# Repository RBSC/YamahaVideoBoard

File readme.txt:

Improved Video Board for Yamaha MSXs version 1.2
Copyright (c) 2016-2023 RBSC

About
-----

This is the improved video board for Yamaha YIS503II, YIS503III and similar MSX/MSX2 computers to replace the original video
boards or the older versions of the video boards from RBSC. The changes to the v1.2 board comparing to the previous verions are:

- Allows to use either CXA1675 or CXA2075 video encoder chips
- Contains an improved YTRAP filter
- Allows to use through-hole electrolytic capacitors (see note below)
- Allows to switch between on-board and internal MSX's 3.58MHz clock generator for NTSC
- Allows to disable one or both on-board clock generators
- Requires less components if CXA2075 encoder is used
- If using only computer's 3.58Mhz and NTSC, there's no need to assemble both clock generators

It is possible to use some components from the old black-and-white video board from the YIS503IIIR computer to build the v1.2
board. The following components can be re-used:

- 330uF capacitors (4)
- 10uF capacitors (4)
- 2sc1684 transistors (4)
- 100uF capacitors (2)
- DIN8 female socket
- Male 13-pin connector for motherboard's cable

IMPORTANT! When installing 100uF capacitors from the original board, please make sure to install the 16v rated capacitor as C3
and the 10v rated capacitor as C2. Otherwise, the 10v rated capacitor installed as C3 may blow up!

WARNING!
--------

Do not install ONBOARD and EXT jumpers at the same time! When using the EXT jumper, disable both NTSC and PAL clock generators
with their respective jumpers (see below).

The pinout of the RGB connector on the new video board differs from the original pinout! On the new board pin 3 is connected to
+12v supply. When making RGB to SCART cables or when using such cables designed for the Japanese MSX mashines, please make sure
that you connect the +12v to the correct SCART pin - pin 8. Connecting +12v to this pin will switch the TV/monitor to 4:3 mode.

DO NOT connect the cable from Yamaha YIS805 to this video board! The pin order is different on the YIS805 and you will damage
the board if you connect it to YIS805!

It is advised to power down the computer before switching between PAL and NTSC in order to avoid damage to the encoder chip.

Settings
--------

Compared to v1.1 of the videoboard, there are more jumpers. The jumpers labeled as PAL or NTSC DISABLE are used to disable the
on-board PAL or NTSC clock generators and use the internal computer's 3.58MHz clock for NTSC encoding. The installed jumper
disables the clock generator.

The ONBOARD and EXT jumpers are used to select which clock to use for NTSC encoding. When using the EXT jumper, the computer's
internal 3.58MHz clock will be fed to the encoder chip. This will effectively eliminate all color atrefacts in the composite
video output. But this will work only with NTSC mode. The installed jumper enables either on-board or external clock signal.
Never install both jumpers at the same time! Please note that the jumper settings do not affect the RGB output.

There are three 3-pin mode selection jumpers on the video board. These jumpers are used to set the color encoding for the S-Video
and composite video outputs. All 3 jumpers must be set the same way. When the pins 1-2 of the jumpers are shorted, the NTSC
encoding is enabled. Otherwise, when pins 2-3 of the jumpers are shorted, the PAL encoding is enabled. Please note that the
jumper settings do not affect the RGB output.

When setting up the board, it's recommended to measure the voltages on the outputs of 4 potentiometers (variable resistors). The
measurement should be done on the central pin. The correct voltage setting is required to form the stable picture on the
composite video and S-Video outputs.

When using the CXA1675 encoder chip, the recommended voltage for the CSYNC variable resistor is 1.3v, the recommended voltages
for Red, Green and Blue variable resistors are from 1.5v to 2.0v, depending on the desired brightness. The voltages on R, G and
B channels must be the same to avoid color distortion. Each color should be tuned after setting it as background color - for
example when setting the blue color's voltage, use the "color15,4,4" command in Basic to set blue as background color. For
green color use the "color15,2,2" command and for red color use the "color15,6,6" command.

When using the CXA2075 encoder chip, the voltage for CSYNC variable resistor should be set to 1.5v and the voltages for Red,
Green and Blue variable resistors should be set up to 3.0v to reach the desired brightness.

Notes
-----

When using the CXA2075 video encoder, it's not neccessary to install the following elements: C22, C23, C26, C27, R25, R29, R30.
Also, if L1 is not installed, please bridge its solder pads with a wire. However, it's highly recommended to use L1 for better
results.

When planning to use only NTSC encoding with the internal MSX's clock, it may not be necessary to install both oscillators,
both trim capacitors, 74HCT04 chip, C31, C13, C19, R17, R20, R23, as well as optional capacitors on the back side of the board.

Please use the following oscillators: 3.579MHz for NTSC and 4.433MHz for PAL. Using other oscillators may cause undesired side
effects.

It is recommended to use the 74HCT04 chip for the frequency generator circuit. The HC series chips may also work, but the HCT
series is highly recommended.

There may be artefacts on the color transitions in the composite video's output when using the on-board clock generators. These
artefacts can be removed by carefully adjusting the corresponding trim capacitors (C14 or C20) with a small flat screwdriver. 

The sharpness of the composite video output can be adjusted by the C23 trim capacitor that is marked as "YTRAP". Please use a
small flat screwdriver with an isolated handle to trim the capacitors, otherwise interference will occur.

If you are using a jumper pin header instead of the original cable connector, be careful to connect the cable from the MSX's
main board correctly. Incorrect cable connection may damage the video board and your MSX computer!

IMPORTANT!
----------

The RBSC provides all the files and information for free, without any liability (see the disclaimer.txt file). The provided information,
software or hardware must not be used for commercial purposes unless permitted by the RBSC. Producing a small amount of bare boards for
personal projects and selling the rest of the batch is allowed without the permission of RBSC.

When the sources of the tools are used to create alternative projects, please always mention the original source and the copyright!

Contact information
-------------------

The members of RBSC group Tnt23, Wierzbowsky, Pyhesty, Ptero, GreyWolf, SuperMax, VWarlock and DJS3000 can be contacted via the group's
e-mail address:

info@rbsc.su

The group's coordinator could be reached via this e-mail address:

admin@rbsc.su

The group's website can be found here:

https://rbsc.su/
https://rbsc.su/ru

The RBSC's hardware repository can be found here:

https://github.com/rbsc

The RBSC's 3D model repository can be found here:

https://www.thingiverse.com/groups/rbsc/things

-= ! MSX FOREVER ! =-

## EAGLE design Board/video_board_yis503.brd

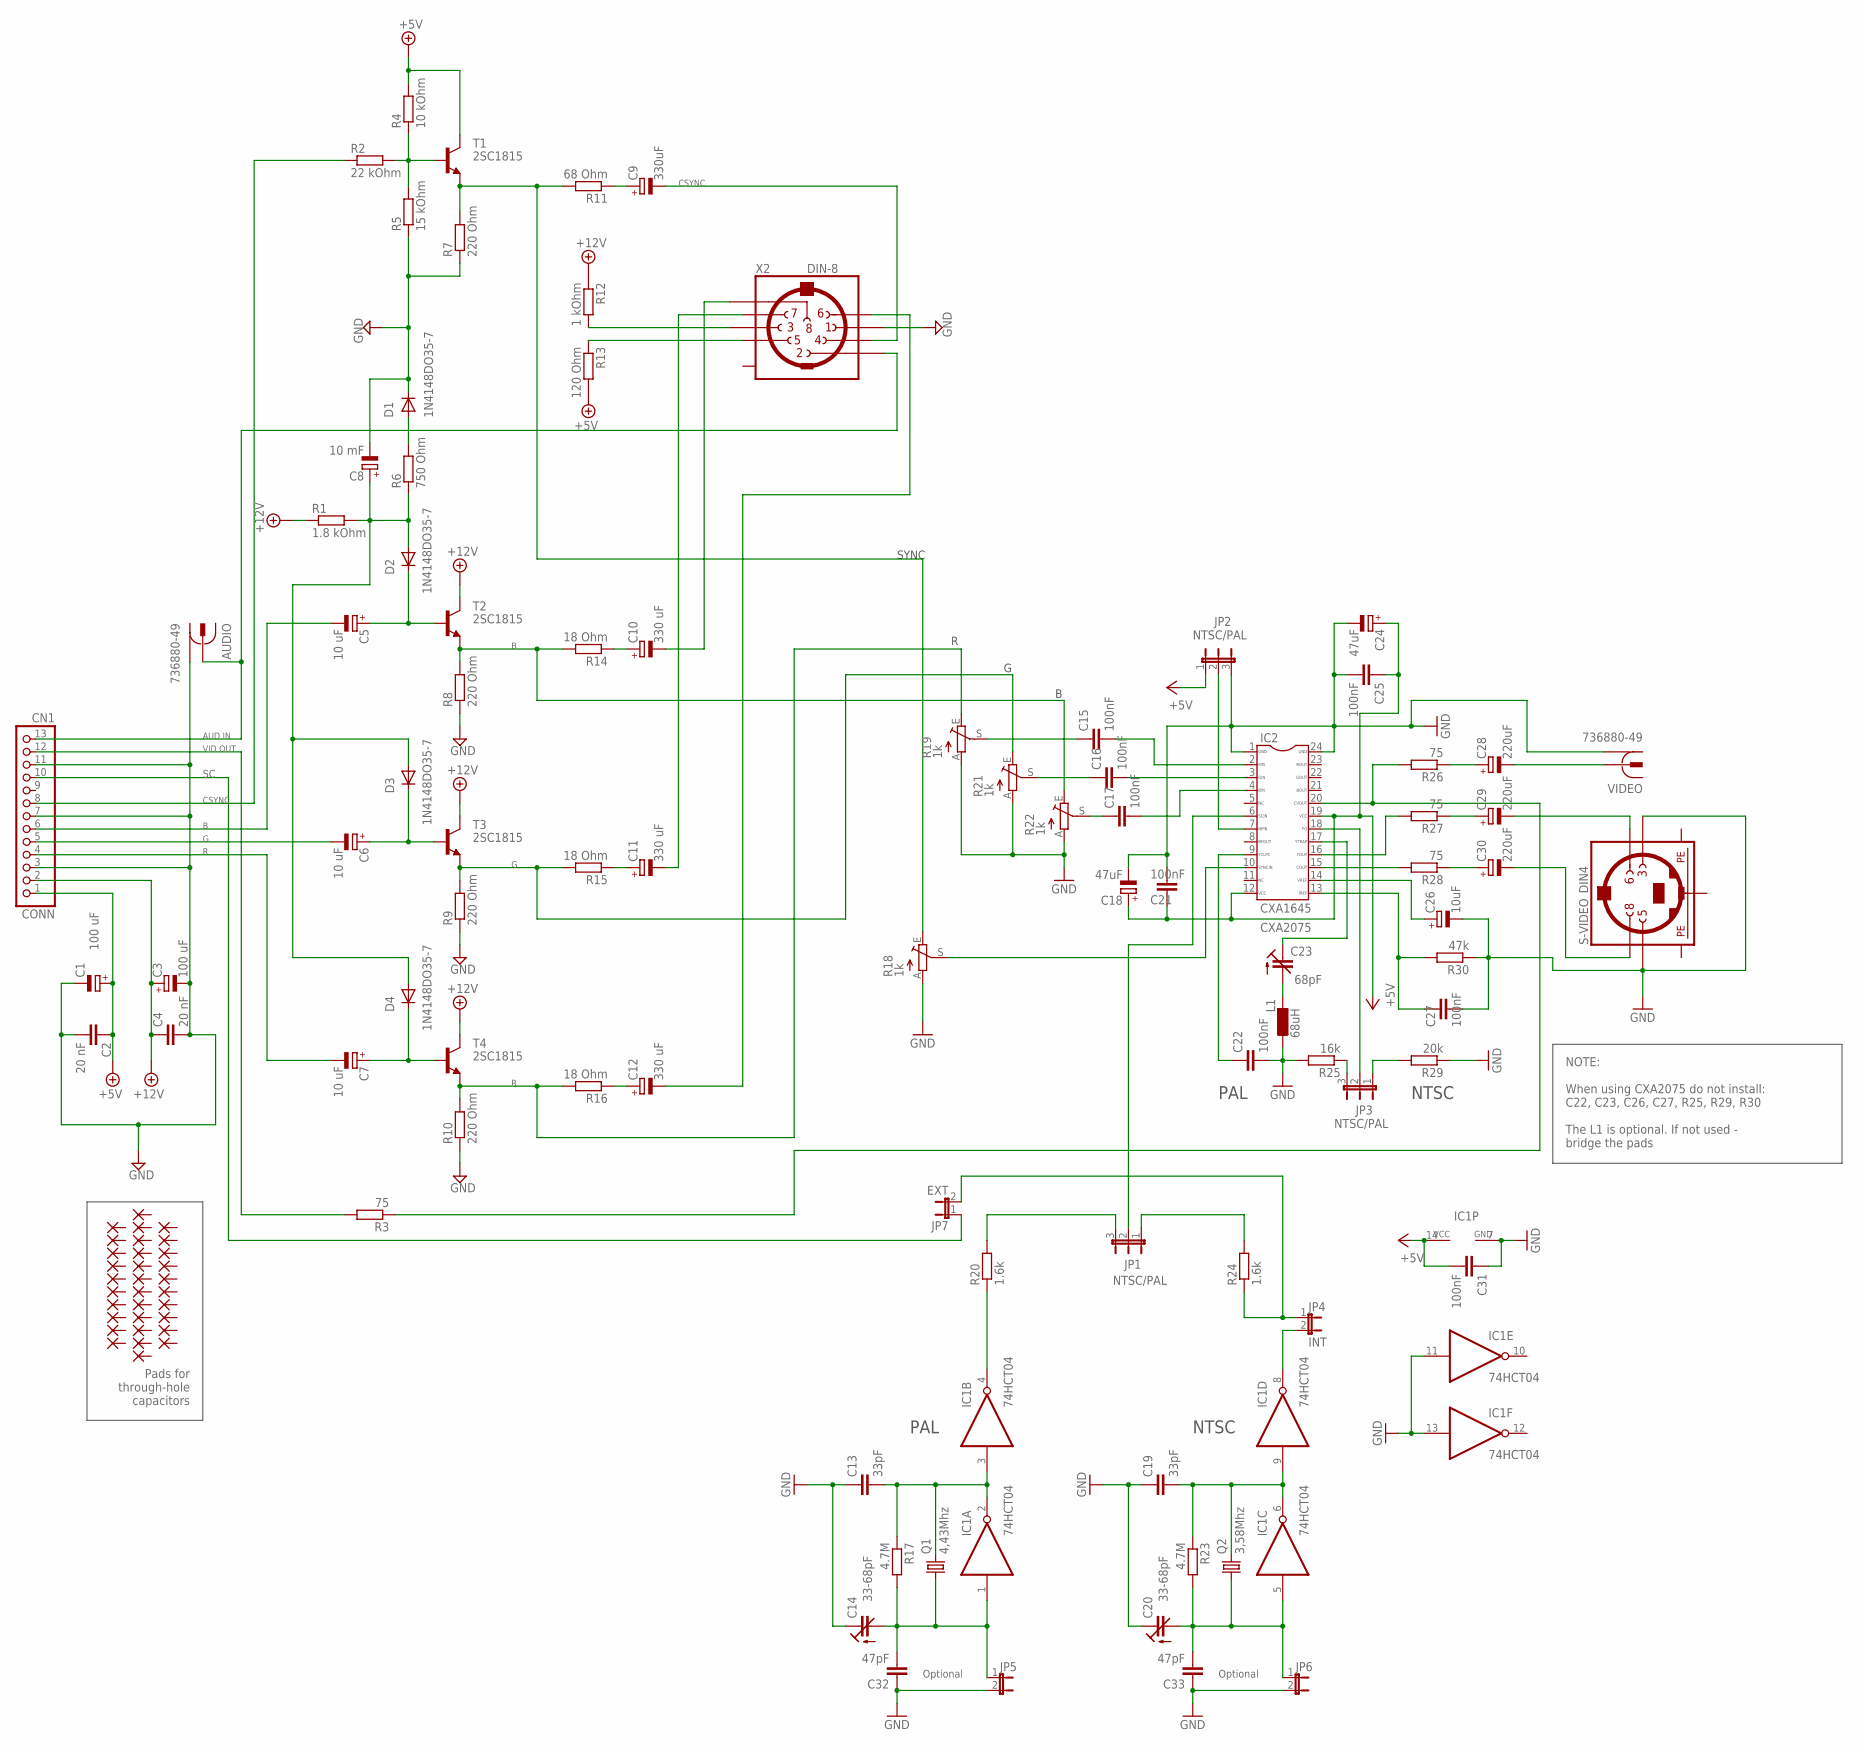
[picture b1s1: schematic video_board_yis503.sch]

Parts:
AUDIO: 736880-49
C1, C3: 100 uF; SMC_D
C2, C4: 20 nF; C0805
C5, C6, C7: 10 uF; SMC_B
C8: 10 mF; SMC_B
C9: 330uF; SMC_D
C10, C11, C12: 330 uF; SMC_D
C13, C19: 33pF; C0805
C14, C20: 33-68pF; CTRIMTZ03
C15, C16, C17, C21, C22, C25, C27, C31: 100nF; C0805
C18, C24: 47uF; SMC_B
C23: 68pF; CTRIMTZ03
C26: 10uF; SMC_B
C28, C29, C30: 220uF; SMC_D
C32, C33: 47pF; C0805
CONN: CN1; 1X13
D1, D2, D3, D4: 1N4148DO35-7; MINIMELF
IC1: 74HCT04; SO14
IC2: CXA1645; SOP24
JP1, JP2, JP3: NTSC/PAL; JP2
JP4: INT; JP1
JP5, JP6: JP1E; JP1
JP7: EXT; JP1
L1: 68uH; L3230M
P1, P2, P3, P4, P5, P6, P7, P8, P9, P10, P11, P12, P13, P14, P15, P16, P17, P18, P19, P20, P21, P22, P23, P24, P25, P26, P27, P28, P29, P30, P31, P32: PADTH
Q1: 4,43Mhz; HC49/S; MPN HC49SM-3.6864-30-50-60-16-ATF
Q2: 3,58Mhz; HC49/S; MPN HC49SM-3.6864-30-50-60-16-ATF
R1: 1.8 kOhm; R0805
R2: 22 kOhm; R0805
R3, R26, R27, R28: 75; R0805
R4: 10 kOhm; R0805
R5: 15 kOhm; R0805
R6: 750 Ohm; R0805
R7, R8, R9, R10: 220 Ohm; R0805
R11: 68 Ohm; R0805
R12: 1 kOhm; R0805
R13: 120 Ohm; R0805
R14, R15, R16: 18 Ohm; R0805
R17, R23: 4.7M; R0805
R18, R19, R21, R22: 1k; CA6V
R20, R24: 1.6k; R0805
R25: 16k; R0805
R29: 20k; R0805
R30: 47k; R0805
S-VIDEO: DIN4; M_DIN4
T1, T2, T3, T4: 2SC1815; TO92-ECB
VIDEO: 736880-49
X2: DIN-8; DIN8

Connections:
+5V: C1.+, C2.1, C18.+, C21.1, C24.+, C25.1, C31.2, CONN.1, IC1.14 (VCC), IC2.12, IC2.19, JP2.1, R4.2, R13.2, T1.C
+12V: C3.+, C4.1, CONN.2, R1.1, R12.1, T2.C, T3.C, T4.C
GND: AUDIO.1, AUDIO.1@1 (1), AUDIO.1@2 (1), C1.-, C2.2, C3.-, C4.2, C8.-, C13.1, C14.1 (E), C18.-, C19.1, C20.1 (E), C21.2, C22.2, C24.-, C25.2, C26.-, C27.2, C31.1, C32.1, C33.1, CONN.3, CONN.7, CONN.11, D1.C, IC1.7 (GND), IC1.11 (I), IC1.13 (I), IC2.1, IC2.24, JP2.3, JP5.2, JP6.2, L1.2, R5.1, R7.1, R8.1, R9.1, R10.1, R18.A, R19.A, R21.A, R22.A, R25.2, R29.1, R30.1, S-VIDEO.3, S-VIDEO.5, VIDEO.1, VIDEO.1@1 (1), VIDEO.1@2 (1), X2.1
unnamed: R10.2, R16.2, R19.E, T4.E
unnamed: C20.2 (A), C33.2, IC1.5 (I), JP6.1, Q2.1, R23.2
unnamed: JP4.1, JP7.2, R24.1
unnamed: CONN.8, R2.1
unnamed: R8.2, R14.2, R22.E, T2.E
unnamed: C15.1, R19.S
unnamed: C16.1, R21.S
unnamed: IC1.4 (O), R20.1
unnamed: C23.2 (A), L1.1
unnamed: C19.2, IC1.6 (O), IC1.9 (I), Q2.2, R23.1
unnamed: JP1.3, R20.2
unnamed: C8.+, D2.A, D3.A, D4.A, R1.2, R6.1
unnamed: JP3.3, R25.1
unnamed: IC2.7, JP2.2
unnamed: JP3.1, R29.2
unnamed: IC2.16, R27.2
unnamed: JP1.1, R24.2
unnamed: IC1.8 (O), JP4.2
unnamed: CONN.12, R3.2
unnamed: C23.1 (E), IC2.17
unnamed: C12.-, X2.6
unnamed: C11.-, X2.7
unnamed: C6.+, D3.C, T3.B
unnamed: C10.-, X2.8
unnamed: D1.A, R6.2
unnamed: C6.-, CONN.5
unnamed: C5.-, CONN.6
unnamed: AUDIO.2, CONN.13, X2.2
unnamed: C12.+, R16.1
unnamed: R12.2, X2.3
unnamed: R9.2, R15.2, R21.E, T3.E
unnamed: R13.1, X2.5
unnamed: C7.+, D4.C, T4.B
unnamed: C7.-, CONN.4
unnamed: C5.+, D2.C, T2.B
unnamed: R2.2, R4.1, R5.2, T1.B
unnamed: R7.2, R11.2, R18.E, T1.E
unnamed: C11.+, R15.1
unnamed: C10.+, R14.1
unnamed: C9.+, R11.1
unnamed: C9.-, X2.4
unnamed: C17.1, R22.S
unnamed: C16.2, IC2.3
unnamed: C15.2, IC2.2
unnamed: C17.2, IC2.4
unnamed: C14.2 (A), C32.2, IC1.1 (I), JP5.1, Q1.1, R17.2
unnamed: C13.2, IC1.2 (O), IC1.3 (I), Q1.2, R17.1
unnamed: IC2.10, R18.S
unnamed: IC2.6, JP1.2
unnamed: IC2.20, R3.1, R26.2
unnamed: C22.1, IC2.9
unnamed: IC2.18, JP3.2
unnamed: IC2.15, R28.2
unnamed: C28.+, R26.1
unnamed: C29.+, R27.1
unnamed: C30.+, R28.1
unnamed: C26.+, IC2.14
unnamed: C27.1, IC2.13, R30.2
unnamed: C28.-, VIDEO.2
unnamed: C29.-, S-VIDEO.6
unnamed: C30.-, S-VIDEO.8
PE1: S-VIDEO.SH1 (PE1)
PE2: S-VIDEO.SH2 (PE2)
PE3: S-VIDEO.SH3 (PE3)
SC: CONN.10, JP7.1

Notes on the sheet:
CSYNC
AUD IN
VID OUT
SYNC
PAL
NTSC
Optional
Pads for through-hole capacitors
CXA2075
NOTE: When using CXA2075 do not install: C22, C23, C26, C27, R25, R29, R30 The L1 is optional. If not used - bridge the pads

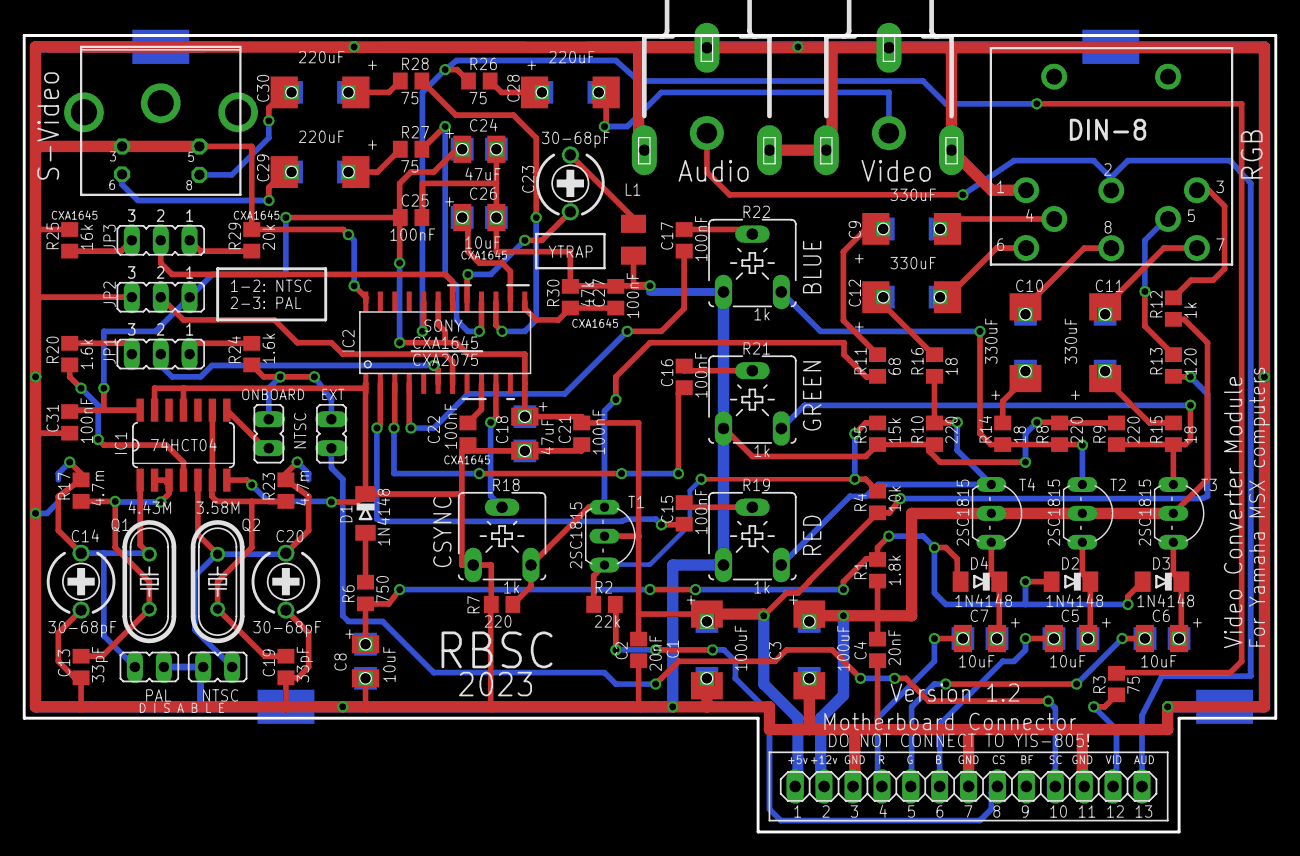
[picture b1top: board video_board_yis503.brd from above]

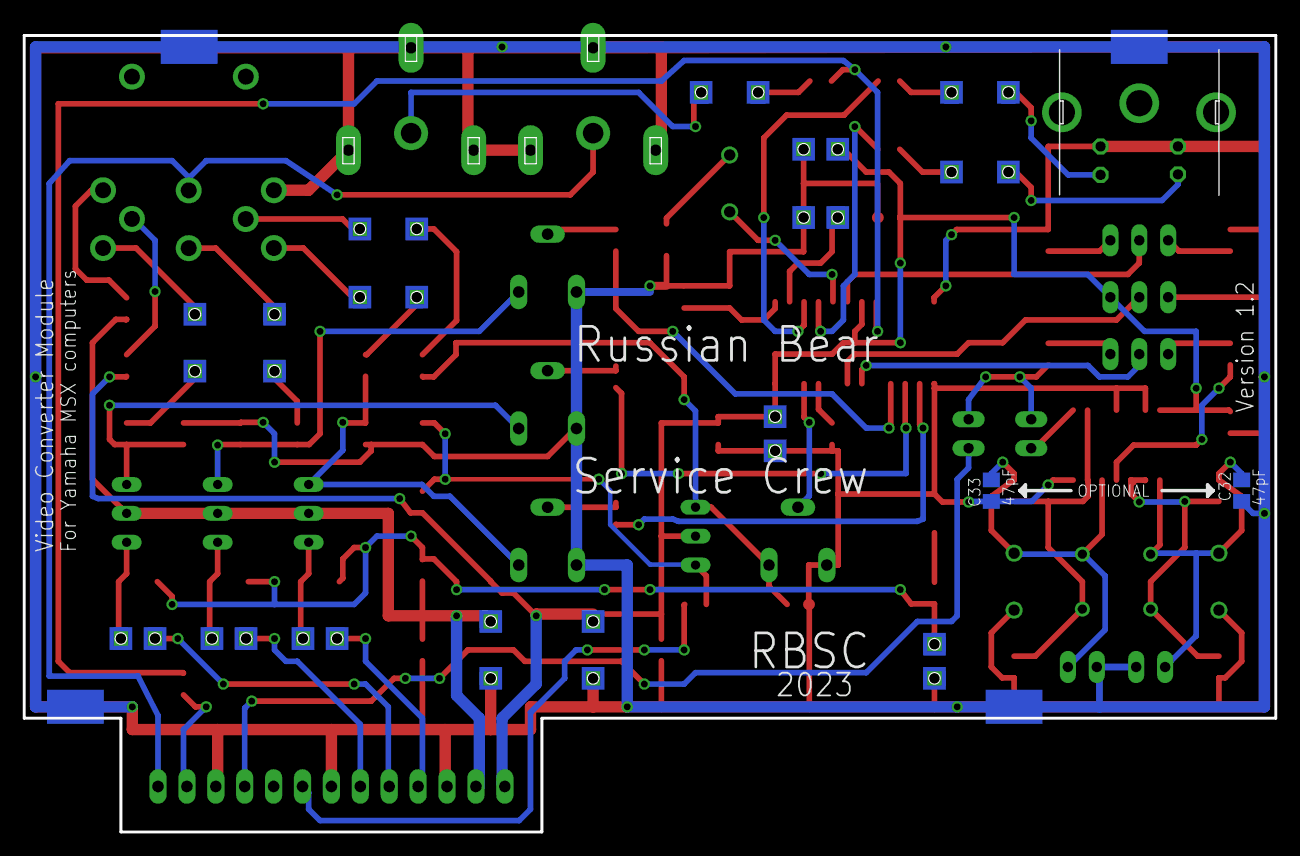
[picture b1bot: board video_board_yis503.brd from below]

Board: 2 copper layers, 110.0 x 70.0 mm, 120 parts (2 on the bottom side), 65 nets.

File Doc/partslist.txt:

Improved Video Board for Yamaha MSXs version 1.1
Copyright (c) 2016 RBSC

Partlist
--------

Assembly variant: 

Part     Value          Package   Library    Position (mm)         Orientation	Notes

AUDIO    736880-49      736880-49 con-conrad (60 65)               R270		Use Yamaha's own output (RCA)
C1       100 uF         SMC_D     rcl        (60 16)               R270		16v or more!
C2       20 nF          C0805     rcl        (54 16)               R270
C3       100 uF         SMC_D     rcl        (69 16)               R270		16v or more!
C4       20 nF          C0805     rcl        (75 16)               R270
C5       10 uF          SMC_B     rcl        (92 17)               R180		10v or more
C6       10 uF          SMC_B     rcl        (100 17)              R180		10v or more
C7       10 uF          SMC_B     rcl        (84 17)               R180		10v or more
C8       10 uF          SMC_B     rcl        (30 15)               R270		10v or more
C9       330 uF         SMC_D     rcl        (78 53)               R0		10v or more
C10      330 uF         SMC_D     rcl        (88 43)               R90		10v or more
C11      330 uF         SMC_D     rcl        (95 43)               R90		10v or more
C12      330 uF         SMC_D     rcl        (78 47)               R0		10v or more
C13      33pF           C0805     rcl        (5 14.5)              R90
C14      33-68pF        CTRIMTZ03 rcl        (5 22)                R180
C15      100nF          C0805     rcl        (58 28)               R270
C16      100nF          C0805     rcl        (58 40)               R270
C17      100nF          C0805     rcl        (58 52)               R270
C18      47uF           SMC_B     rcl        (44 35)               R270		10v or more
C19      33pF           C0805     rcl        (23 14.5)             R90
C20      33-68pF        CTRIMTZ03 rcl        (23 22)               R180
C21      100nF          C0805     rcl        (49 35)               R270
C22      100nF          C0805     rcl        (39 35)               R270
C23      68pF           CTRIMTZ03 rcl        (48 57)               R180
C24      47uF           SMC_B     rcl        (40 60)               R0		10v or more
C25      100nF          C0805     rcl        (34 54)               R0
C26      10uF           SMC_B     rcl        (40 54)               R0		10v or more
C27      100nF          C0805     rcl        (52 47)               R90
C28      220uF          SMC_D     rcl        (48 65)               R0		10v or more
C29      220uF          SMC_D     rcl        (26 58)               R180		10v or more
C30      220uF          SMC_D     rcl        (26 65)               R180		10v or more
C31      100nF          C0805     rcl        (4 36)                R90
C32      47pF           C0805     rcl        (3 30)                MR90		(optional, back side)
C33      47pF           C0805     rcl        (25 30)               MR90		(optional, back side)
CONN     CN1            1X13      pinhead    (83 4)                R0
D1       1N4148DO35-7   MINIMELF  diode      (30 28)               R270
D2       1N4148DO35-7   MINIMELF  diode      (92 22)               R180
D3       1N4148DO35-7   MINIMELF  diode      (100 22)              R180
D4       1N4148DO35-7   MINIMELF  diode      (84 22)               R180
IC1      74HCT04        SO14      74xx-eu    (14 34)               R0
IC2      CXA1645        SOP24     CXA1645M   (37 43)               R0
JP1      NTSC/PAL       JP2       jumper     (12 42)               R180
JP2      NTSC/PAL       JP2       jumper     (12 47)               R180
JP3      NTSC/PAL       JP2       jumper     (12 52)               R180
Q1       4,43Mhz        HC49/S    crystal    (11 22)               R270
Q2       3,58Mhz        HC49/S    crystal    (17 22)               R270
R1       1.8 kOhm       R0805     resistor   (75 23)               R90
R2       22 kOhm        R0805     resistor   (51 20)               R180
R3       75             R0805     rcl        (96 13)               R270
R4       10 kOhm        R0805     resistor   (75 29)               R270
R5       15 kOhm        R0805     resistor   (75 35)               R90
R6       750 Ohm        R0805     resistor   (30 21)               R90
R7       220 Ohm        R0805     resistor   (42 20)               R0
R8       220 Ohm        R0805     resistor   (91 35)               R270
R9       220 Ohm        R0805     resistor   (96 35)               R270
R10      220 Ohm        R0805     resistor   (80 35)               R90
R11      68 Ohm         R0805     resistor   (75 41)               R270
R12      1 kOhm         R0805     resistor   (101 46)              R90
R13      120 Ohm        R0805     resistor   (101 41)              R270
R14      18 Ohm         R0805     resistor   (86 35)               R270
R15      18 Ohm         R0805     resistor   (101 35)              R270
R16      18 Ohm         R0805     resistor   (80 41)               R270
R17      4.7M           R0805     rcl        (5 30)                R90
R18      1k             CA6V      pot        (42 26)               R0
R19      1k             CA6V      pot        (64 26)               R0
R20      1.6k           R0805     rcl        (4 42)                R90
R21      1k             CA6V      pot        (64 38)               R0
R22      1k             CA6V      pot        (64 50)               R0
R23      4.7M           R0805     rcl        (23 30)               R90
R24      1.6k           R0805     rcl        (20 42)               R90
R25      16k            R0805     rcl        (4 52)                R90
R26      75             R0805     rcl        (40 66)               R180
R27      75             R0805     rcl        (34 60)               R0
R28      75             R0805     rcl        (34 66)               R0
R29      20k            R0805     rcl        (20 52)               R270
R30      47k            R0805     rcl        (48 47)               R270
S-VIDEO  DIN4           M_DIN4    mini_din   (12 64)               R0
T1       2SC1815        TO92-ECB  transistor (51 26)               R270
T2       2SC1815        TO92-ECB  transistor (93 28)               R270
T3       2SC1815        TO92-ECB  transistor (101 28)              R270
T4       2SC1815        TO92-ECB  transistor (85 28)               R270
VIDEO    736880-49      736880-49 con-conrad (76 65)               R270		Use Yamaha's own output (RCA)
X2       DIN-8          DIN8      din8       (96 60)               R180

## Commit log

2016-07-19 :tada: Added .gitattributes & .gitignore files
2016-07-19 Board version 1.1
    Yamaha video board version 1.1
2017-05-20 Added readme files
2017-08-31 Latest fixes for schematics and partslist
    Fixed incorrect C8 value in partslist and schematics
2018-08-07 Updated readme 07.08.2018
    Updated readme 07.08.2018
2019-03-05 Updated 05.03.2019
    Added exact oscillator values for PAL and NTSC
2019-10-22 Updated 22.10.2019
    Updated readme, read the warning carefully!
2023-02-09 Release 09.02.2023
    Video board v1.2 release
2023-02-09 Release 09.02.2023
    Updated readme
2023-02-10 Release 09.02.2023
    Updated the assembled board's picture
2023-06-06 Updated 06.06.2023
    Fixed a few non-critical typos in the documentation

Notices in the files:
Board/video_board_yis503.sch:
Copyright (c) 2016-2023 by RBSC
